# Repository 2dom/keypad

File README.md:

# Zigbee Touch Keypad

I wanted a door keypad that actually looked good on the wall — slim, wireless, no visible screws, no cloud dependency. Something I could mount next to the front door, punch in a code, and have Home Assistant react instantly. Off-the-shelf Zigbee keypads exist, but they're usually expensive, mains-powered, or locked to one ecosystem. So I built my own.

The result is a battery-powered touch keypad about the size of a pez dispenser. It runs for roughly **six months** on a single charge, talks **Zigbee** to whatever coordinator you already run, and wakes from deep sleep the moment you touch a key. This repo has everything you need to build one yourself: Gerber files, a 3D-printable case, and working firmware.

The firmware ships as a **Zigbee** end-device example. The same **ESP32-C6** board is equally happy running **Matter** or **Thread** — the touch handling and power logic stay the same; only the radio stack changes.

<p align="center">
  
</p>

## What it looks like on the wall

The design goal was something that disappears into a modern entryway. A white slab on textured walls, twelve touch buttons, no mechanics to wear out.

Early renders explored proportions and mounting position before the first PCB arrived. Getting the aspect ratio right mattered — too tall and it looks just weird, too wide and it reads as a light switch.

The front panel is a 2×6 grid: digits **1–9**, **0**, a **clear** key, and **enter**. Labels are printed directly on the PCB solder mask — no separate overlay, no glue, nothing to peel off after two winters.

---

## Tear it down

Pop the case apart and the internals are deliberately simple. A custom backplane PCB, a 1300 mAh LiPo filling most of the volume, and an ESP32-C6 dev board at the bottom with a USB-C port for charging and flashing.

The whole assembly is rather light hence can be mounted to the wall with a few bites of white tack. For scale:

Three layers, top to bottom:

1. **Keypad face** — the touch matrix PCB you see and press
2. **Electronics bay** — battery, ESP32-C6, MPR121 touch controller
3. **Back cover** — 3D-printed shell (`case_mid_final.stl`) that clips on without screws

The onboard LED sits inside the white case that is somewhat translucent. When the device wakes from deep sleep it glows briefly; each key press flashes it again so you always know your touch registered.

---

## Order the PCB

You don't need to lay out a board from scratch. The Gerber files are in this repo and ready to upload to any fab. I've been using [JLCPCB](https://jlcpcb.com) — pick a colour scheme, drop in the matching zip, and order. No CAM fixes, no layer renaming, no back-and-forth with support.

| File | Colour scheme |
|------|---------------|
| `touch_matrix_Y24.zip` | **Black on white** — black key labels on a white PCB (latest revision) |
| `touch_matrix_Y23.zip` | **White on black** — white key labels on a black PCB |

Same layout, same touch pads — only the silkscreen colours differ. Choose whichever fits your wall and enclosure.

The back of the PCB carries the JLC order markings and a five-pin header for the MPR121:

| Pin | Function |
|-----|----------|
| GND | Ground |
| INT | Interrupt (wake from sleep) |
| SCL | I²C clock |
| SDA | I²C data |
| 3.3 V | Power |

---

## Wire it up

The firmware expects this pin mapping on the ESP32-C6 DevKitC-1:

| Signal | GPIO | Notes |
|--------|------|-------|
| I²C SDA | 18 | MPR121 data |
| I²C SCL | 4 | MPR121 clock |
| IRQ | 6 | MPR121 interrupt — also the deep-sleep wake source |
| Battery ADC | 2 | Voltage divider input |
| BOOT button | 9 | Hold 3 s for Zigbee factory reset |

The wiring is very straigtforward - simply connect all the pins as described, connect the battery to ESP32-C6 bat pins, route 3.3V and ground to the PCB and done. If you would like the battery SOC reported, you will need to add an additional voltage device to the battery pins. 

The twelve MPR121 channels map to the front-panel keys like this:

| Channel | Key |
|---------|-----|
| 0–8 | 1 – 9 |
| 9 | 0 |
| 10 | Clear |
| 11 | Enter |

For now the software allows coes up to eight digits.

---

## Flash the firmware

The project builds with [PlatformIO](https://platformio.org/). Clone the repo, connect the ESP32-C6 over USB-C, and:

```bash
pio run --target upload
```

To watch the serial log while pairing:

```bash
pio device monitor
```

The build targets **Zigbee end-device mode** (`ZIGBEE_MODE_ED`) with a custom partition table (`partitions_zigbee.csv`) that reserves flash for Zigbee network storage. Dependencies are pulled automatically — the main one is the Adafruit MPR121 library.

---

## Join your Zigbee network

On first boot the keypad scans for a coordinator. Dots print on the serial console at 115200 baud until it joins. In Home Assistant that means adding it through ZHA or Zigbee2MQTT — the device shows up as manufacturer **DrDoms**, model **KeyPad2**.

Two Zigbee endpoints are exposed:

| Endpoint | Cluster | What it reports |
|----------|---------|-----------------|
| 1 | Analog Input + Battery | Entered passcode, battery voltage |
| 2 | Analog Input | Battery state of charge (%) |

The passcode flow works like this:

1. Touch digits on the pad — the LED confirms each press.
2. Press **Enter**. The code is reported on endpoint 1 as an analog value.
3. Battery level is reported at the same time.
4. Two seconds later the reported value resets to **0**, ready for the next entry.

**Leading 1:** The firmware always prepends a **1** to every code before sending it. The input buffer starts as `"1"` and resets to `"1"` after clear or enter. This is because ensure that leading zeros in your entered code are not stripped as the value is purely numeric, not a string. 

Press **Clear** at any time to wipe the buffer and start over.

### Home Assistant with ZHA

Once the keypad is flashed, getting it into [Home Assistant](https://www.home-assistant.io/) through [ZHA](https://www.home-assistant.io/integrations/zha/) takes about two minutes.

1. In Home Assistant go to **Settings → Devices & Services → Zigbee Home Automation** and open your coordinator.
2. Click **Add device** and confirm — this opens the network for joining.
3. Wake the keypad by touching any key. Within a few seconds it should appear as **DrDoms KeyPad2**.
4. Finish the interview if ZHA asks — no special configuration is needed.

After pairing, open the device page and note the entity names ZHA created. The important one is the **Passcode** analog-input sensor — in my setup it shows up as `sensor.drdoms_keypad2_passcode`. You will also see battery voltage and percentage sensors from the second endpoint. Entity IDs can differ slightly depending on your ZHA version and how many Espressif devices you already have, so always copy the names from your own device page rather than assuming mine.

When you enter a code and press **Enter**, that sensor updates to the numeric value of your input — including the leading **1** described above — holds it for two seconds, then drops back to **0**. That brief window is what your automations listen for.

The file `keypad_automation.yaml` is a worked example that maps passcodes to actions — opening a door, raising a cover, closing a cover. Import it as a starting point and adapt it to your home:

1. Go to **Settings → Automations & Scenes → Create Automation → Edit in YAML** (top-right menu).
2. Paste the contents of `keypad_automation.yaml`, or save the file to your Home Assistant `packages/` folder if you use [packages](https://www.home-assistant.io/docs/configuration/packages/).
3. Replace every `entity_id` with the ones from your installation — the passcode sensor, the door button, the cover, and so on.
4. Change the template values to match the codes you actually want. Each `if` block compares the passcode sensor against a number; when they match, the action runs. Remember to account for the leading **1** — the sample value `12345` means you typed **2-3-4-5** on the pad, not **1-2-3-4-5**. A code you enter as **0-1** will appear as **101** in Home Assistant.

```yaml
# Example: open a cover when passcode 12345 is entered
- if:
    - condition: template
      value_template: "{{ states('sensor.drdoms_keypad2_passcode') | int(0) == 12345 }}"
  then:
    - action: cover.open_cover
      target:
        entity_id: cover.basement_control_cover
```

The sample automation listens on two sensor entities because entity naming changed between ZHA versions — `sensor.espressif_zigbeeanalogdevice_power` is the older name, `sensor.drdoms_keypad2_passcode` is the current one. Keep whichever matches your device and delete the other trigger block.

To find the exact integer your keypad sends for a given code, enter the code, press **Enter**, and watch the sensor in **Developer Tools → States**. Use that number in your template condition.

### Matter and Thread

This repo demonstrates Zigbee because it's the fastest path to a working smart-home integration. But the ESP32-C6 has a native 802.15.4 radio, so porting to **Thread** and **Matter** is straightforward — the touch scanning, debouncing, battery ADC, and deep-sleep wake logic in `main.cpp` don't care which protocol sends the numbers upstream. Espressif's [ESP-Matter](https://github.com/espressif/esp-matter) SDK is the place to start if you want to go that route.

---

## Power: six months on a charge

Battery life was the hardest constraint. A keypad that's dead every two weeks is worse than no keypad at all.

The trick is aggressive deep sleep. After ten seconds without a touch, the firmware shuts everything down and puts the MPR121 into its slowest scan rate. The ESP32-C6 draws almost nothing. The next finger on the pad pulls the MPR121 interrupt line low, the MCU wakes, re-initialises I²C, and is ready to scan within milliseconds.

With a 1300 mAh cell and typical use — a few code entries per day — that works out to roughly **half a year** between USB-C charges. Battery voltage and percentage are reported over Zigbee so you can set a low-battery alert in Home Assistant before it goes flat.

---

## Day-to-day use

1. Walk up and touch a key. The LED glows through the case as the device wakes.
2. Enter your code. Each digit flashes the LED.
3. Press **Enter** to send it to your automation.
4. Walk away. Ten seconds later it sleeps again.

If you need to re-pair — new coordinator, corrupted network, that sort of thing — hold the **BOOT** button for more than three seconds. The device factory-resets its Zigbee stack and reboots.

---

## What's in this repo

```
keypad/
├── main.cpp                  # Touch handling, Zigbee reporting, power management
├── platformio.ini            # Board target, libraries, build flags
├── partitions_zigbee.csv     # Flash layout with Zigbee storage partitions
├── case_mid_final.stl        # 3D-printable enclosure mid-section
├── touch_matrix_Y24.zip      # PCB Gerbers — black on white
├── touch_matrix_Y23.zip      # PCB Gerbers — white on black
├── keypad_automation.yaml    # Home Assistant example — passcode → actions
└── touch_matrix_*.jpg        # Photos from the build
```

---

## License

| Part | License | File |
|------|---------|------|
| Firmware (`main.cpp`, build config) | [MIT License](LICENSE) | `LICENSE` |
| Hardware (PCB Gerbers, STL, design files) | [CERN Open Hardware Licence v2 — Strongly Reciprocal](LICENSE.hardware) | `LICENSE.hardware` |

It really works well - has been my method of entry for the past year. If you make a variant — Matter port, different key layout, waterproof enclosure — I'd love to see it.

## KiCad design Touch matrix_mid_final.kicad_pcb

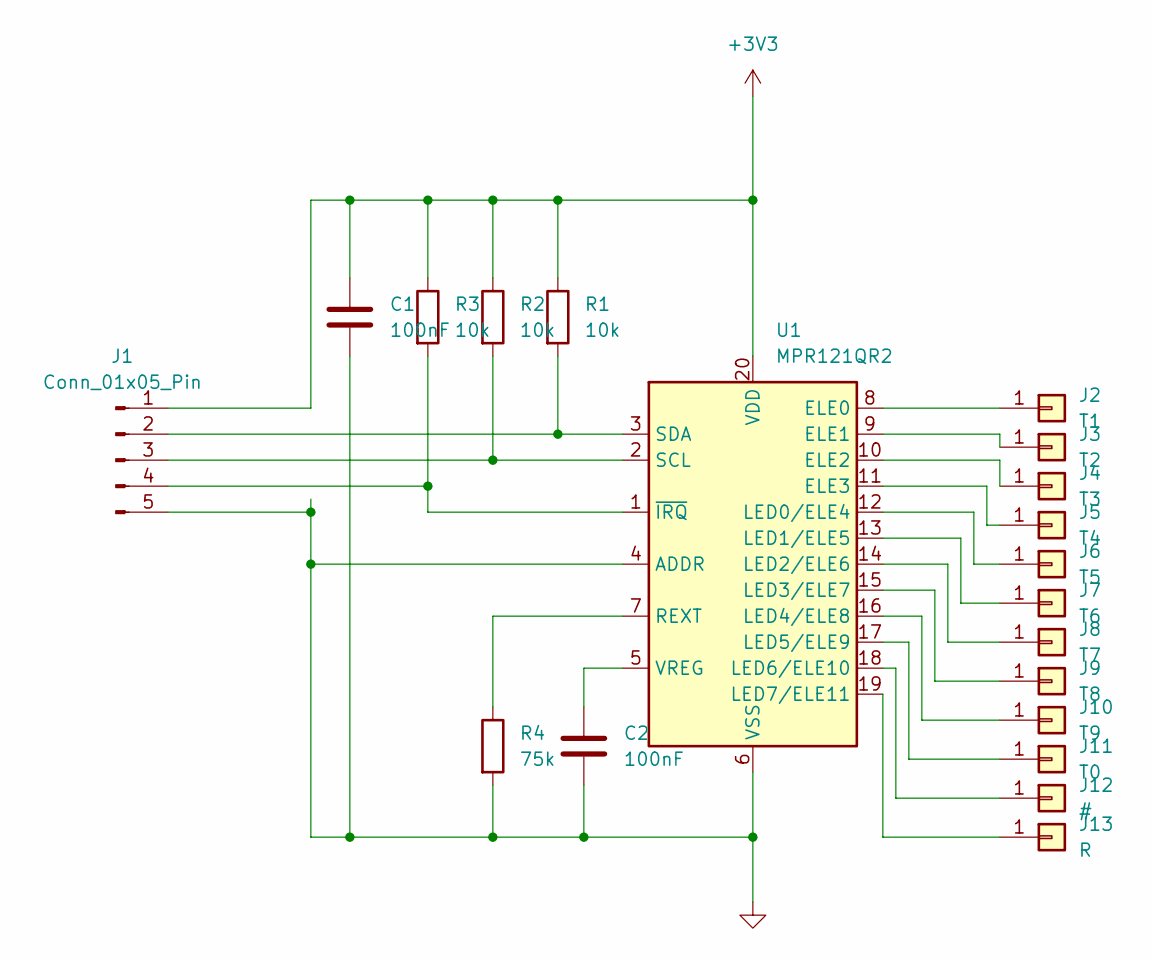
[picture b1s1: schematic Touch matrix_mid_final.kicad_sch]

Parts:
C1, C2: 100nF; C_0603_1608Metric
J1: Conn_01x05_Pin; Molex_CLIK-Mate_502382-0570_1x05-1MP_P1.25mm_Vertical
J2: T1; touch_pad_mod
J3: T2; touch_pad_mod
J4: T3; touch_pad_mod
J5: T4; touch_pad_mod
J6: T5; touch_pad_mod
J7: T6; touch_pad_mod
J8: T7; touch_pad_mod
J9: T8; touch_pad_mod
J10: T9; touch_pad_mod
J11: T0; touch_pad_mod
J12: #; touch_pad_mod
J13: R; touch_pad_mod
R1, R2, R3: 10k; C_0603_1608Metric
R4: 75k; C_0603_1608Metric
U1: MPR121QR2; UQFN-20_3x3mm_P0.4mm

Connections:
+3V3: C1.1, J1.1, R1.1, R2.1, R3.1, U1.20 (VDD)
GND: C1.2, C2.2, J1.5, R4.2, U1.4 (ADDR), U1.6 (VSS)
unnamed: J1.2, R1.2, U1.3 (SDA)
unnamed: J1.3, R2.2, U1.2 (SCL)
unnamed: J1.4, R3.2, U1.1 (~IRQ)
unnamed: J2.1, U1.8 (ELE0)
unnamed: J3.1, U1.9 (ELE1)
unnamed: J4.1, U1.10 (ELE2)
unnamed: J5.1, U1.11 (ELE3)
unnamed: J6.1, U1.12 (LED0/ELE4)
unnamed: J7.1, U1.13 (LED1/ELE5)
unnamed: J8.1, U1.14 (LED2/ELE6)
unnamed: J9.1, U1.15 (LED3/ELE7)
unnamed: J10.1, U1.16 (LED4/ELE8)
unnamed: J11.1, U1.17 (LED5/ELE9)
unnamed: J12.1, U1.18 (LED6/ELE10)
unnamed: J13.1, U1.19 (LED7/ELE11)
unnamed: R4.1, U1.7 (REXT)
unnamed: C2.1, U1.5 (VREG)

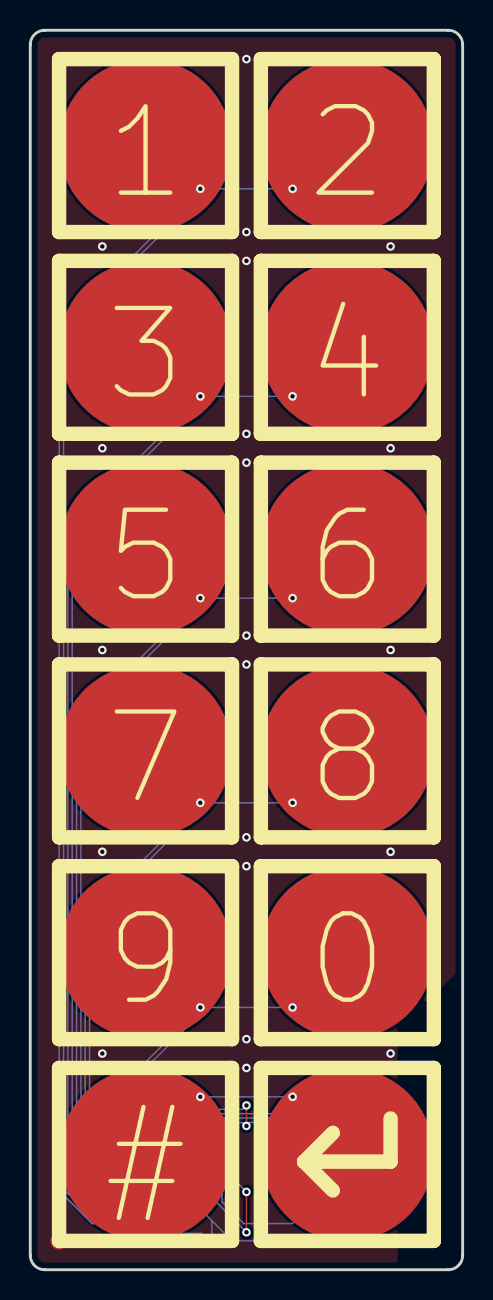
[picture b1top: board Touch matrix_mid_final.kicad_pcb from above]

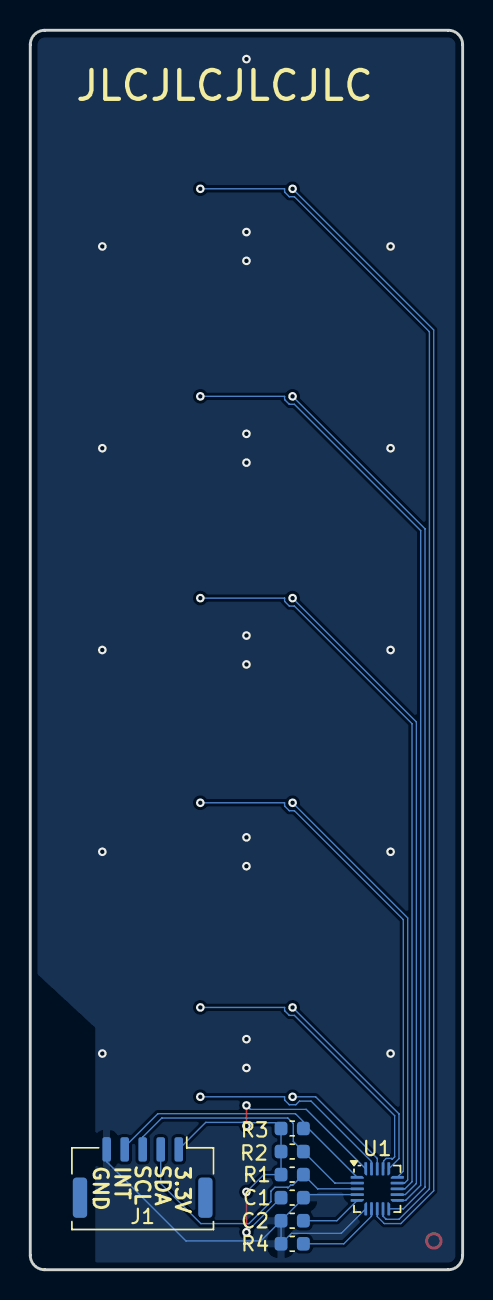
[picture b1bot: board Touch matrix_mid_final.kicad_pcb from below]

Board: 2 copper layers, 30.0 x 86.0 mm, 20 parts (8 on the bottom side), 19 nets.

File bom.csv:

Designator,Footprint,Quantity,Value,LCSC Part #
"C1, C2",0603,2,100nF,
J1,Molex_CLIK-Mate_502382-0570_1x05-1MP_P1.25mm_Vertical,1,Conn_01x05_Pin,
J10,touch_pad_mod,1,T9,
J11,touch_pad_mod,1,T0,
J12,touch_pad_mod,1,#,
J13,touch_pad_mod,1,R,
J2,touch_pad_mod,1,T1,
J3,touch_pad_mod,1,T2,
J4,touch_pad_mod,1,T3,
J5,touch_pad_mod,1,T4,
J6,touch_pad_mod,1,T5,
J7,touch_pad_mod,1,T6,
J8,touch_pad_mod,1,T7,
J9,touch_pad_mod,1,T8,
"R1, R2, R3",0603,3,10k,
R4,0603,1,75k,
U1,UQFN-20_3x3mm_P0.4mm,1,MPR121QR2,

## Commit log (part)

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2026-06-25 initial
2026-06-25 initial2
2026-06-25 initial3
